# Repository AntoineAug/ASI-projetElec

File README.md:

Un réveil intelligent
==============
Dans le cadre de notre scolarité à l'INSA de Rouen nous réalisons un projet d'électronique nommé "Un réveil intelligent" utilisant un Raspberry Pi et une carte Arduino.

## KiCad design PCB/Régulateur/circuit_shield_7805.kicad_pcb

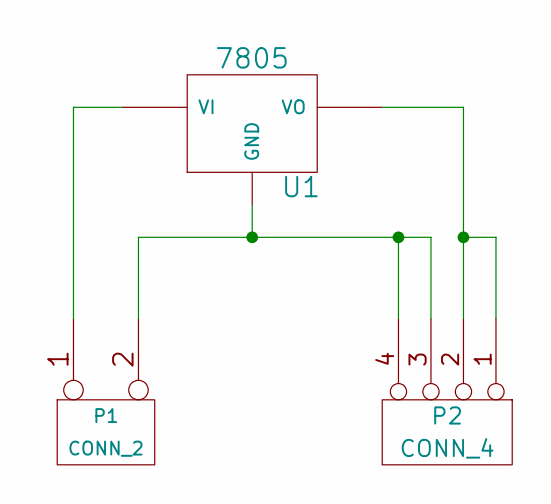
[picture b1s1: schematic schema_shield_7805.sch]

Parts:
P1: CONN_2
P2: CONN_4
U1: 7805

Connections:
unnamed: P1.2 (PM), P2.3, P2.4, U1.GND
unnamed: P2.1, P2.2, U1.VO
unnamed: P1.1, U1.VI

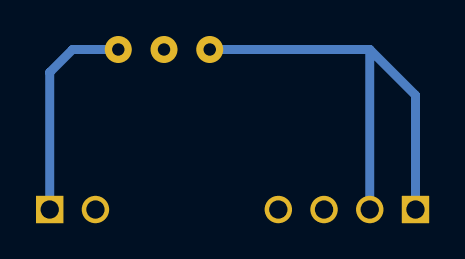
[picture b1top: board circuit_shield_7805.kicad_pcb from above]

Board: 2 copper layers, 3 parts (0 on the bottom side), 3 nets.

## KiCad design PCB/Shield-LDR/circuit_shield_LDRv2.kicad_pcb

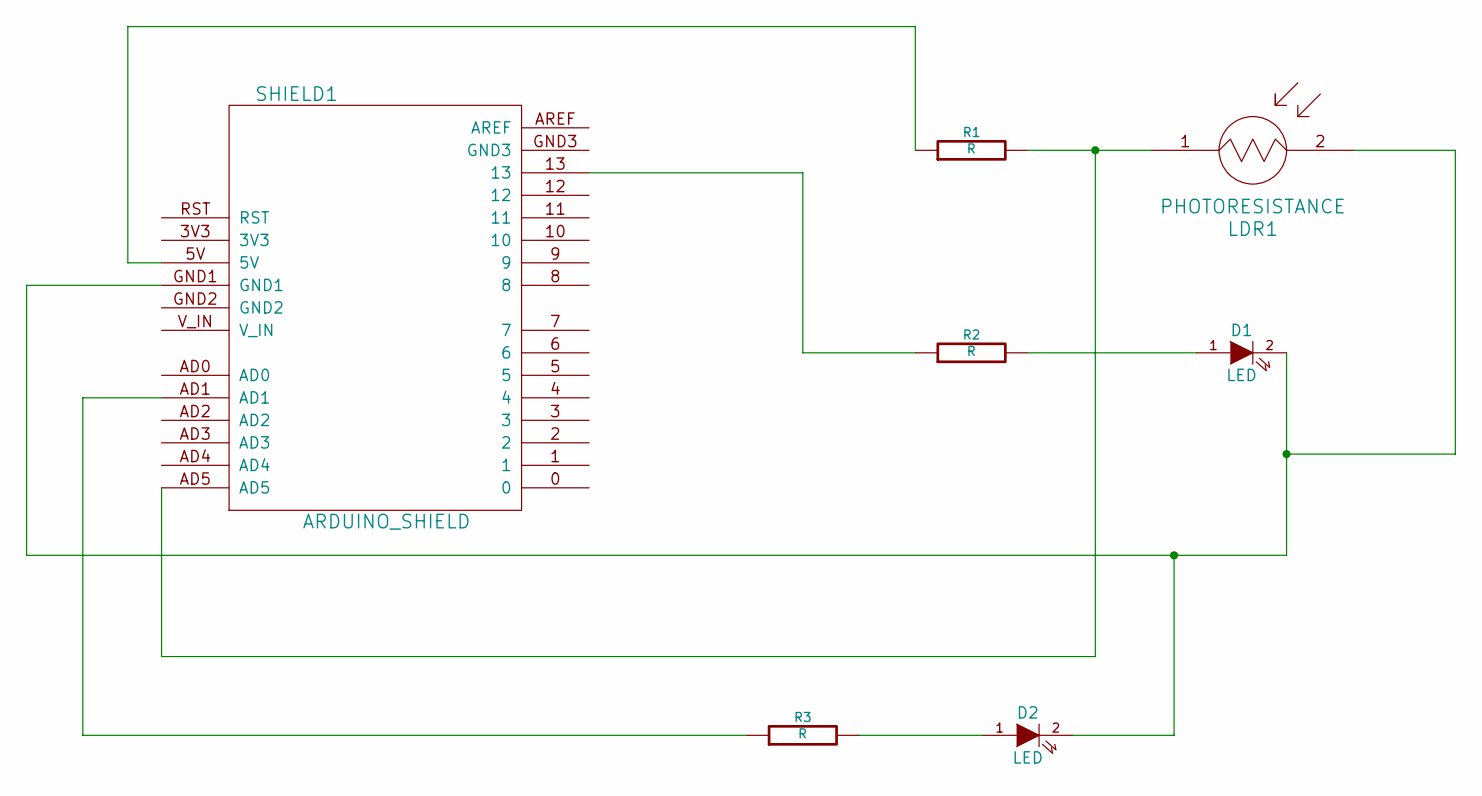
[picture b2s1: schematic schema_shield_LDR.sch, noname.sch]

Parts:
D1, D2: LED
LDR1: PHOTORESISTANCE
R1, R2, R3: R
SHIELD1: ARDUINO_SHIELD

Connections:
unnamed: D1.2 (K), D2.2 (K), LDR1.2, SHIELD1.GND1
unnamed: R1.1, SHIELD1.5V
unnamed: R2.1, SHIELD1.13
unnamed: D2.1 (A), R3.2
unnamed: R3.1, SHIELD1.AD1
unnamed: D1.1 (A), R2.2
unnamed: LDR1.1, R1.2, SHIELD1.AD5

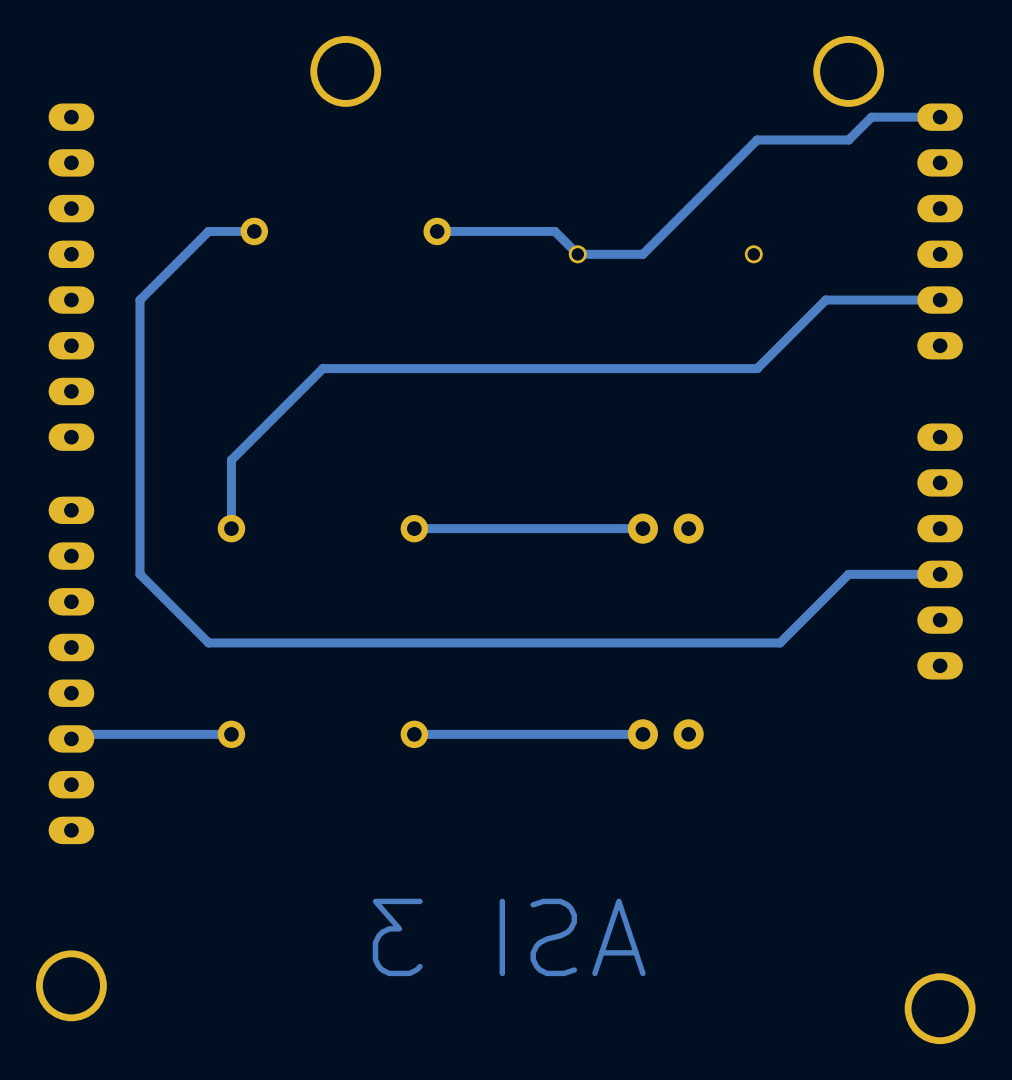
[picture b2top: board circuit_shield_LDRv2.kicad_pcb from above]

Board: 2 copper layers, 7 parts (0 on the bottom side), 7 nets.

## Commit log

2013-10-09 Back up vm asi
2013-10-09 Ajout des images concernant l'électronique
2013-10-09 Suppression des fichiers propres à OS X
2013-10-09 MàJ du README
2013-10-09 Suppression fichiers temporaires LaTex
2013-10-09 Ajout du .gitignore
2013-10-09 Ajout du cahier des charges
2013-10-09 Calendrier previsionnel
2013-10-09 Un peu de rangement
2013-10-09 Petit renommage
2013-10-09 Ajout du dossier PCB
2013-10-09 Ajout du code Arduino
2013-10-09 Ajout des librairies dans le dossier PCB
2013-10-23 cahier de suivi pdf
2013-10-23 Ajout du bon de commande
2013-10-23 Maj du bon de commande
2013-10-23 note calendrier previsionnel
2013-10-23 Résolution de bug sur la destination
2013-10-23 Cahier de suivi mercredi 23 Octobre 2013
2013-10-23 MàJ du bon de commande
2013-10-23 modifs code test integration
2013-10-23 Bon de commande final
2013-10-29 Ajout d'une led au montage
2013-11-10 Réorganisation des dossiers dans PCB et ajout du CI régulateur de tension
2013-11-11 maj Calendrier prévisionnel
2013-11-13 modifications erreurs dates calendrier-prévisionnel
2013-11-13 Fade lampe
2013-11-13 Calendrier-Previsionnel maj dates
2013-11-13 maj cahier de suivi 13 novembre 2013
2013-11-15 Devoir
2013-11-16 Version finale partie elec (Shield LDR & CI Regulateur)
2013-11-27 Cahier de suivi, mercredi 27 Novembre 2013
2013-12-11 Mercredi 11 décembre
2013-12-28 Début rédaction rapport final
2013-12-28 Lisibilité
2013-12-28 Rajout d'une section réseau pour Raspberry
2013-12-28 Ajout d'un paragraphe à propos du gestionnaire de sons
2013-12-28 Rajout du bon de commande
2014-01-01 Ajout des partie etude technique et document de réalisation
2014-01-01 organisation du dossier images
2014-01-03 Code Arduino
2014-01-03 Communication Arduino - Raspberry
2014-01-04 Rajout de l'étude technique dans le rapport
2014-01-04 Première ébauche de conclusion
2014-01-04 Ajout de photos
2014-01-04 Inclusion des photos dans les annexes
2014-01-05 Ajout de l'Intro
2014-01-05 Nouvelle image de fond
2014-01-05 Typo
2014-01-05 Organisation du rapport
2014-01-05 Modification emplacement des figures + tassage du rapport
2014-01-05 Partie sur le logiciel Arduino
2014-01-06 Plus de photos dans l'annexe / rajout du nom du prof
2014-01-06 Mis à jour du chaier de suivi
2014-01-06 Suppression dossier devoir
2014-01-06 Renommage de dossiers / ajout de code / ajout de photos
2014-01-06 Introduction en anglais dans le rapport
2014-01-06 Ajout du PCB livrable
2014-01-07 Ajout de la présentation finale
2014-01-07 Ajout de la partie elec sur la présentation
2014-01-07 Slide Arduino
2014-01-07 Suppression du pdf
2014-01-07 Typo et précisions supplémentaires
2014-01-10 Ajout des livrables finaux
